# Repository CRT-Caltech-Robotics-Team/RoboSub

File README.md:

[RoboSub documentation](https://caltechroboticsteam.github.io/RoboSub/)

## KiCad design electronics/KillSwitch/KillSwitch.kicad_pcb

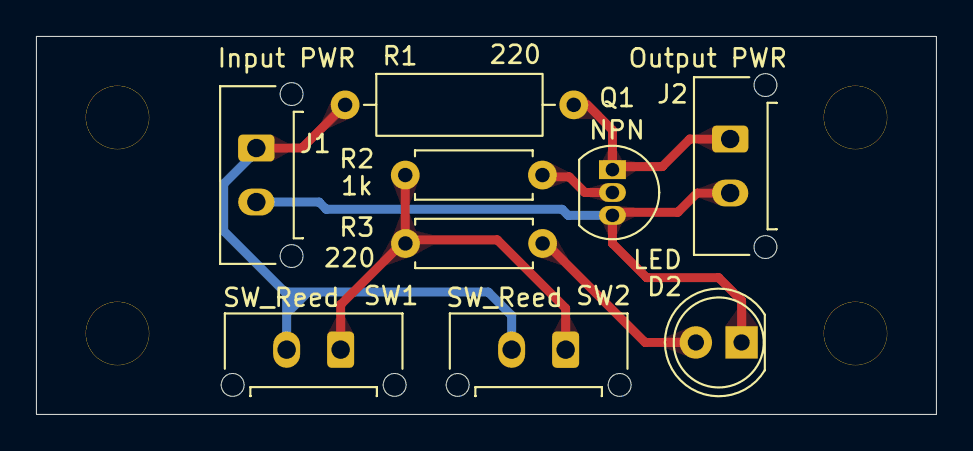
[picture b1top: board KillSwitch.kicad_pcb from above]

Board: 2 copper layers, 50.0 x 21.0 mm, 9 parts (0 on the bottom side), 6 nets.

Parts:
D2: LED; LED_D5.0mm
J1: Input PWR; Molex_Micro-Fit_3.0_43650-0215_1x02_P3.00mm_Vertical
J2: Output PWR; Molex_Micro-Fit_3.0_43650-0215_1x02_P3.00mm_Vertical
Q1: NPN; TO-92_Inline
R1: 220; R_Axial_DIN0309_L9.0mm_D3.2mm_P12.70mm_Horizontal
R2: 1k; R_Axial_DIN0207_L6.3mm_D2.5mm_P7.62mm_Horizontal
R3: 220; R_Axial_DIN0207_L6.3mm_D2.5mm_P7.62mm_Horizontal
SW1, SW2: SW_Reed; Molex_Micro-Fit_3.0_43650-0215_1x02_P3.00mm_Vertical

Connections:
+5V: J1.1, R1.1, SW1.2, SW2.2
GND: D2.1 (K), J1.2, J2.2, Q1.3 (E)
unnamed: D2.2 (A), R3.2
unnamed: J2.1, Q1.1 (C), R1.2
unnamed: Q1.2 (B), R2.2
unnamed: R2.1, R3.1, SW1.1, SW2.1

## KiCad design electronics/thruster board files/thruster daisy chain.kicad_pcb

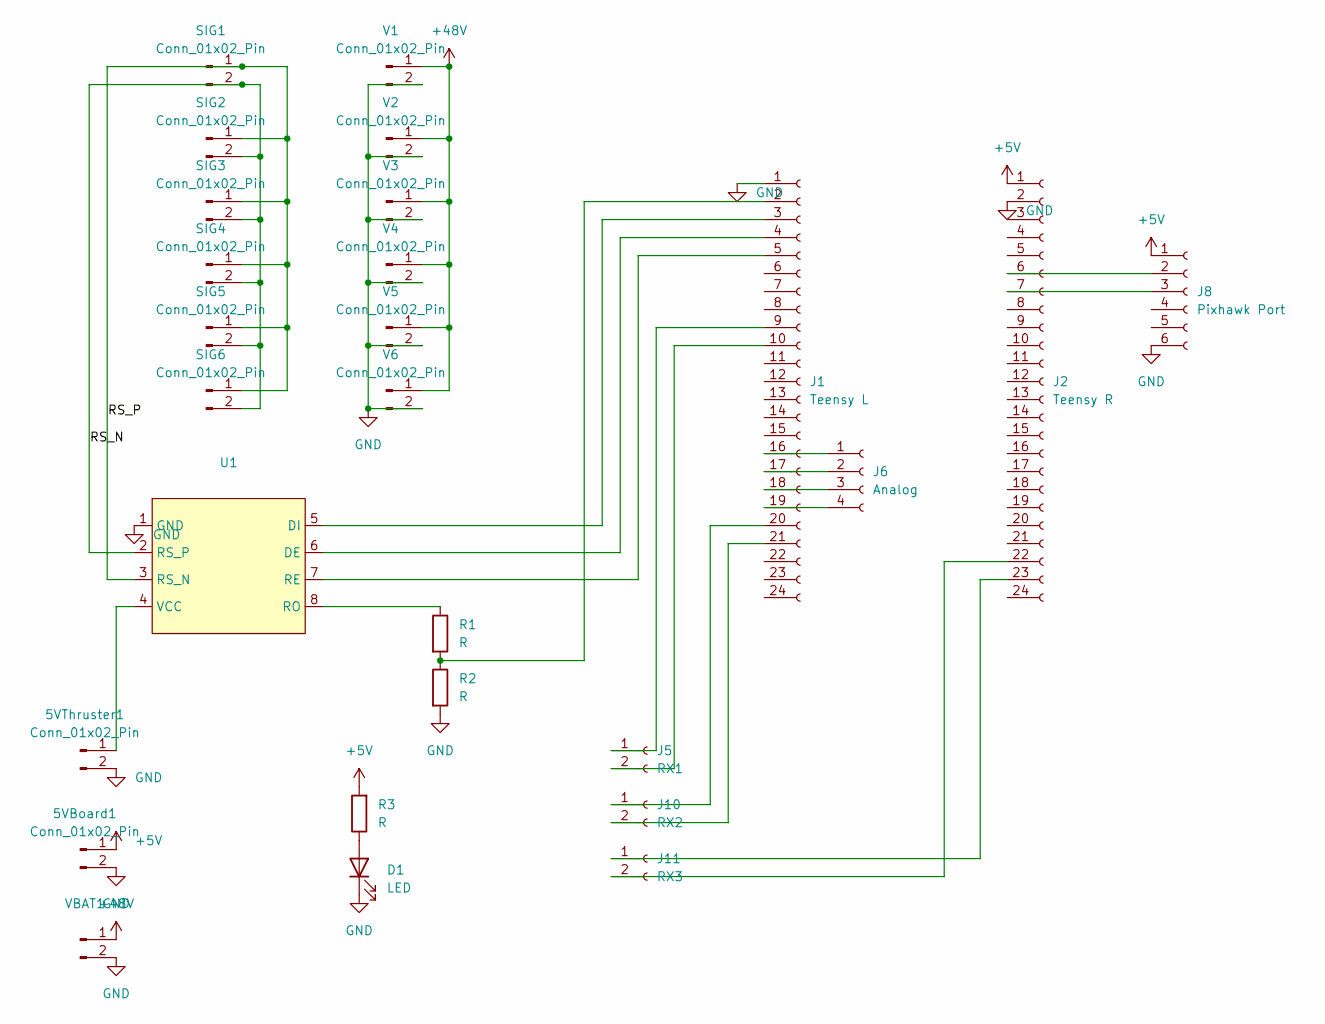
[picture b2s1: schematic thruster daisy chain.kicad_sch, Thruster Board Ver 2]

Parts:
5VBoard1, 5VThruster1: Conn_01x02_Pin; Molex_Micro-Fit_3.0_43650-0215_1x02_P3.00mm_Vertical
D1: LED; LED_0805_2012Metric_Pad1.15x1.40mm_HandSolder
J1: Teensy L; PinHeader_1x24_P2.54mm_Vertical
J2: Teensy R; PinHeader_1x24_P2.54mm_Vertical
J5: RX1; JST_EH_B2B-EH-A_1x02_P2.50mm_Vertical
J6: Analog; PinSocket_1x04_P2.54mm_Vertical
J8: Pixhawk Port; Hirose_DF13-06P-1.25DSA_1x06_P1.25mm_Vertical
J10: RX2; JST_EH_B2B-EH-A_1x02_P2.50mm_Vertical
J11: RX3; JST_EH_B2B-EH-A_1x02_P2.50mm_Vertical
R1, R2, R3: R; C_0805_2012Metric_Pad1.18x1.45mm_HandSolder
SIG1, SIG2, SIG3, SIG4, SIG5, SIG6: Conn_01x02_Pin; JST_EH_B2B-EH-A_1x02_P2.50mm_Vertical
U1: MAX485
V1, V2, V3, V4, V5, V6: Conn_01x02_Pin; Molex_Micro-Fit_3.0_43650-0215_1x02_P3.00mm_Vertical
VBAT1: Conn_01x02_Pin; AMASS_XT60-M_1x02_P7.20mm_Vertical

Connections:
+5V: 5VBoard1.1, J2.1, J8.1, R3.2; also elsewhere on the board
+48V: V1.1, V2.1, V3.1, V4.1, V5.1, V6.1, VBAT1.1
/RS_N: SIG1.2, SIG2.2, SIG3.2, SIG4.2, SIG5.2, SIG6.2, U1.2 (RS_P)
/RS_P: SIG1.1, SIG2.1, SIG3.1, SIG4.1, SIG5.1, SIG6.1, U1.3 (RS_N)
GND: 5VBoard1.2, 5VThruster1.2, D1.1 (K), J1.1, J2.2, J8.6, R2.2, U1.1 (GND), V1.2, V2.2, V3.2, V4.2, V5.2, V6.2, VBAT1.2; also elsewhere on the board
unnamed 5: 5VThruster1.1, U1.4 (VCC); also elsewhere on the board
unnamed: D1.2 (A), R3.1
unnamed: J1.2, R1.2, R2.1
unnamed: J1.3, U1.5 (DI)
unnamed: J1.4, U1.6 (DE)
unnamed: J1.5, U1.7 (RE)
unnamed: J1.9, J5.1
unnamed: J1.10, J5.2
unnamed: J1.16, J6.1
unnamed: J1.17, J6.2
unnamed: J1.18, J6.3
unnamed: J1.19, J6.4
unnamed: J1.20, J10.1
unnamed: J1.21, J10.2
unnamed: J2.6, J8.2
unnamed: J2.7, J8.3
unnamed: J2.23, J11.1
unnamed: J2.22, J11.2
unnamed: R1.1, U1.8 (RO)

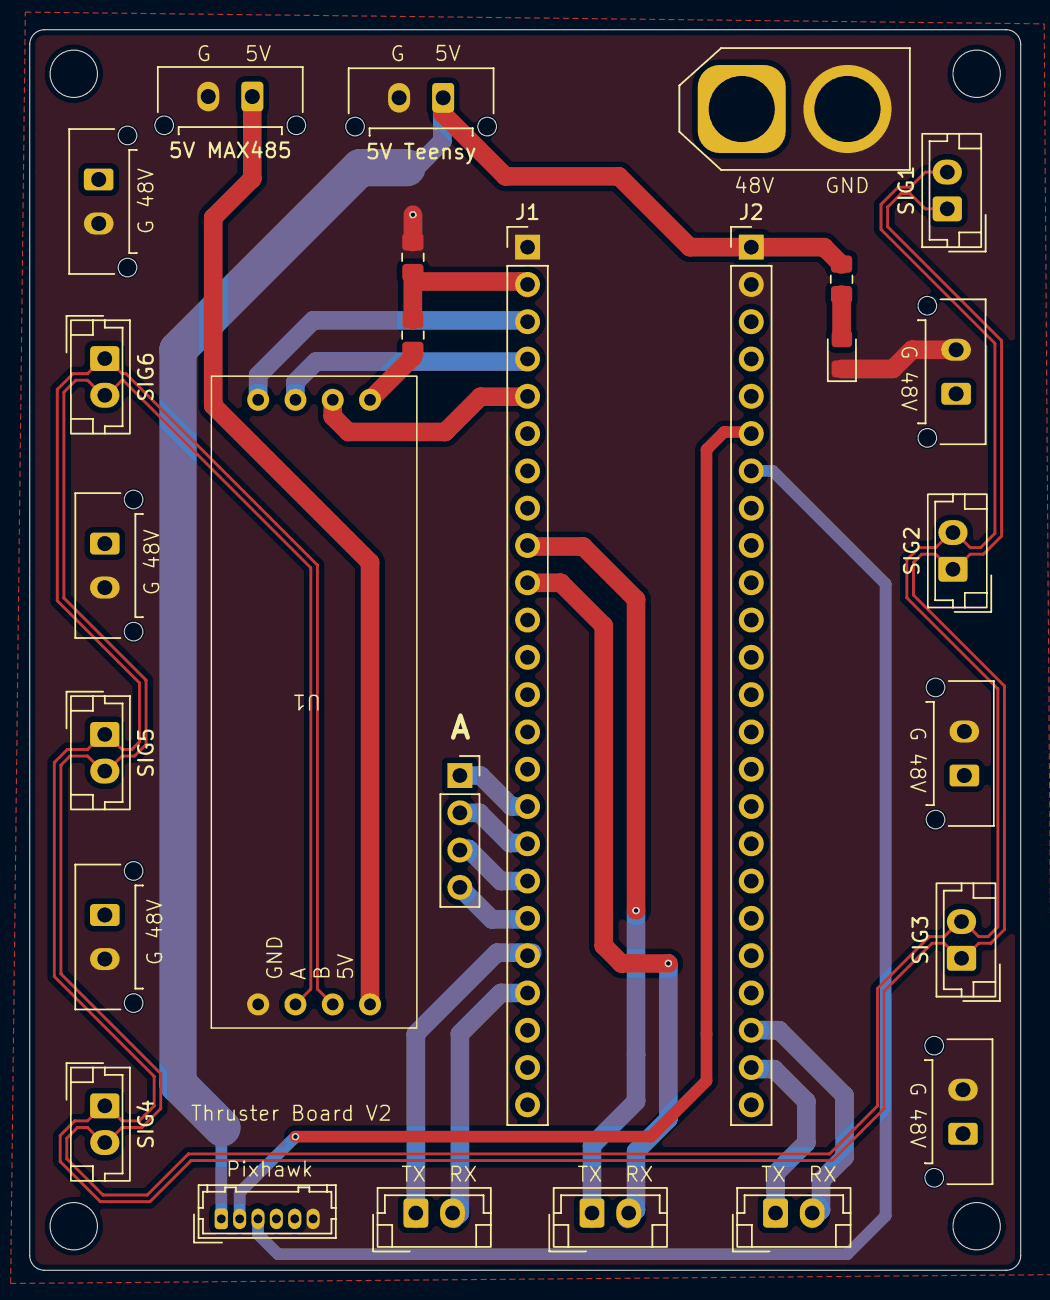
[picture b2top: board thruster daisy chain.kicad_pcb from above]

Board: 4 copper layers, 67.5 x 84.5 mm, 27 parts (0 on the bottom side), 24 nets.

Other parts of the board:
5V MAX485, 5V Teensy: Conn_01x02_Pin; Molex_Micro-Fit_3.0_43650-0215_1x02_P3.00mm_Vertical

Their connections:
+5V: 5V Teensy.1; also elsewhere on the board
GND: 5V MAX485.2, 5V Teensy.2; also elsewhere on the board
unnamed 5: 5V MAX485.1; also elsewhere on the board

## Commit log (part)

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2026-06-20 Current Code
    DVL, Depth sensor, Thrusters
    Depth Sensor and thrusters have MavLink connection.
    DVL has ROS2 node setup (will work on MavLink this weekend, hopefully).
